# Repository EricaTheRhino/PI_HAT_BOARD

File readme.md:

# Erica HAT
A raspberry pi HAT containing the interfaces used on Erica.
This board has the hardware for all of Erica's functions, however only some will be populated on each pi

## Board modules

* **ID EEPROM** as per the hat specification.
* **Button and Status Indicator** to provide information on the state of the pi.
* **DC Input** allows powering of the pi through the HAT.
* **GPIO Breakout** an 8P8C connector containing broken out GPIO, used for the touch sensors.
* **Temperature Sensor** for measuring Erica's internal temperature.
* **Real Time Clock** maintains a time reference when Erica is powered off.
* **Webcam Led Controller** controls the brightness on the eye webcam LEDs also has USB passthough to the webcam.
* **Servo Connector** for connecting the eye servos (directly connected to gpio for use with servoblaster).
* **DMX Interface** for controlling DMX fixtures from the pi.
* **Debug USB-serial** connects to the pi's console for debugging.

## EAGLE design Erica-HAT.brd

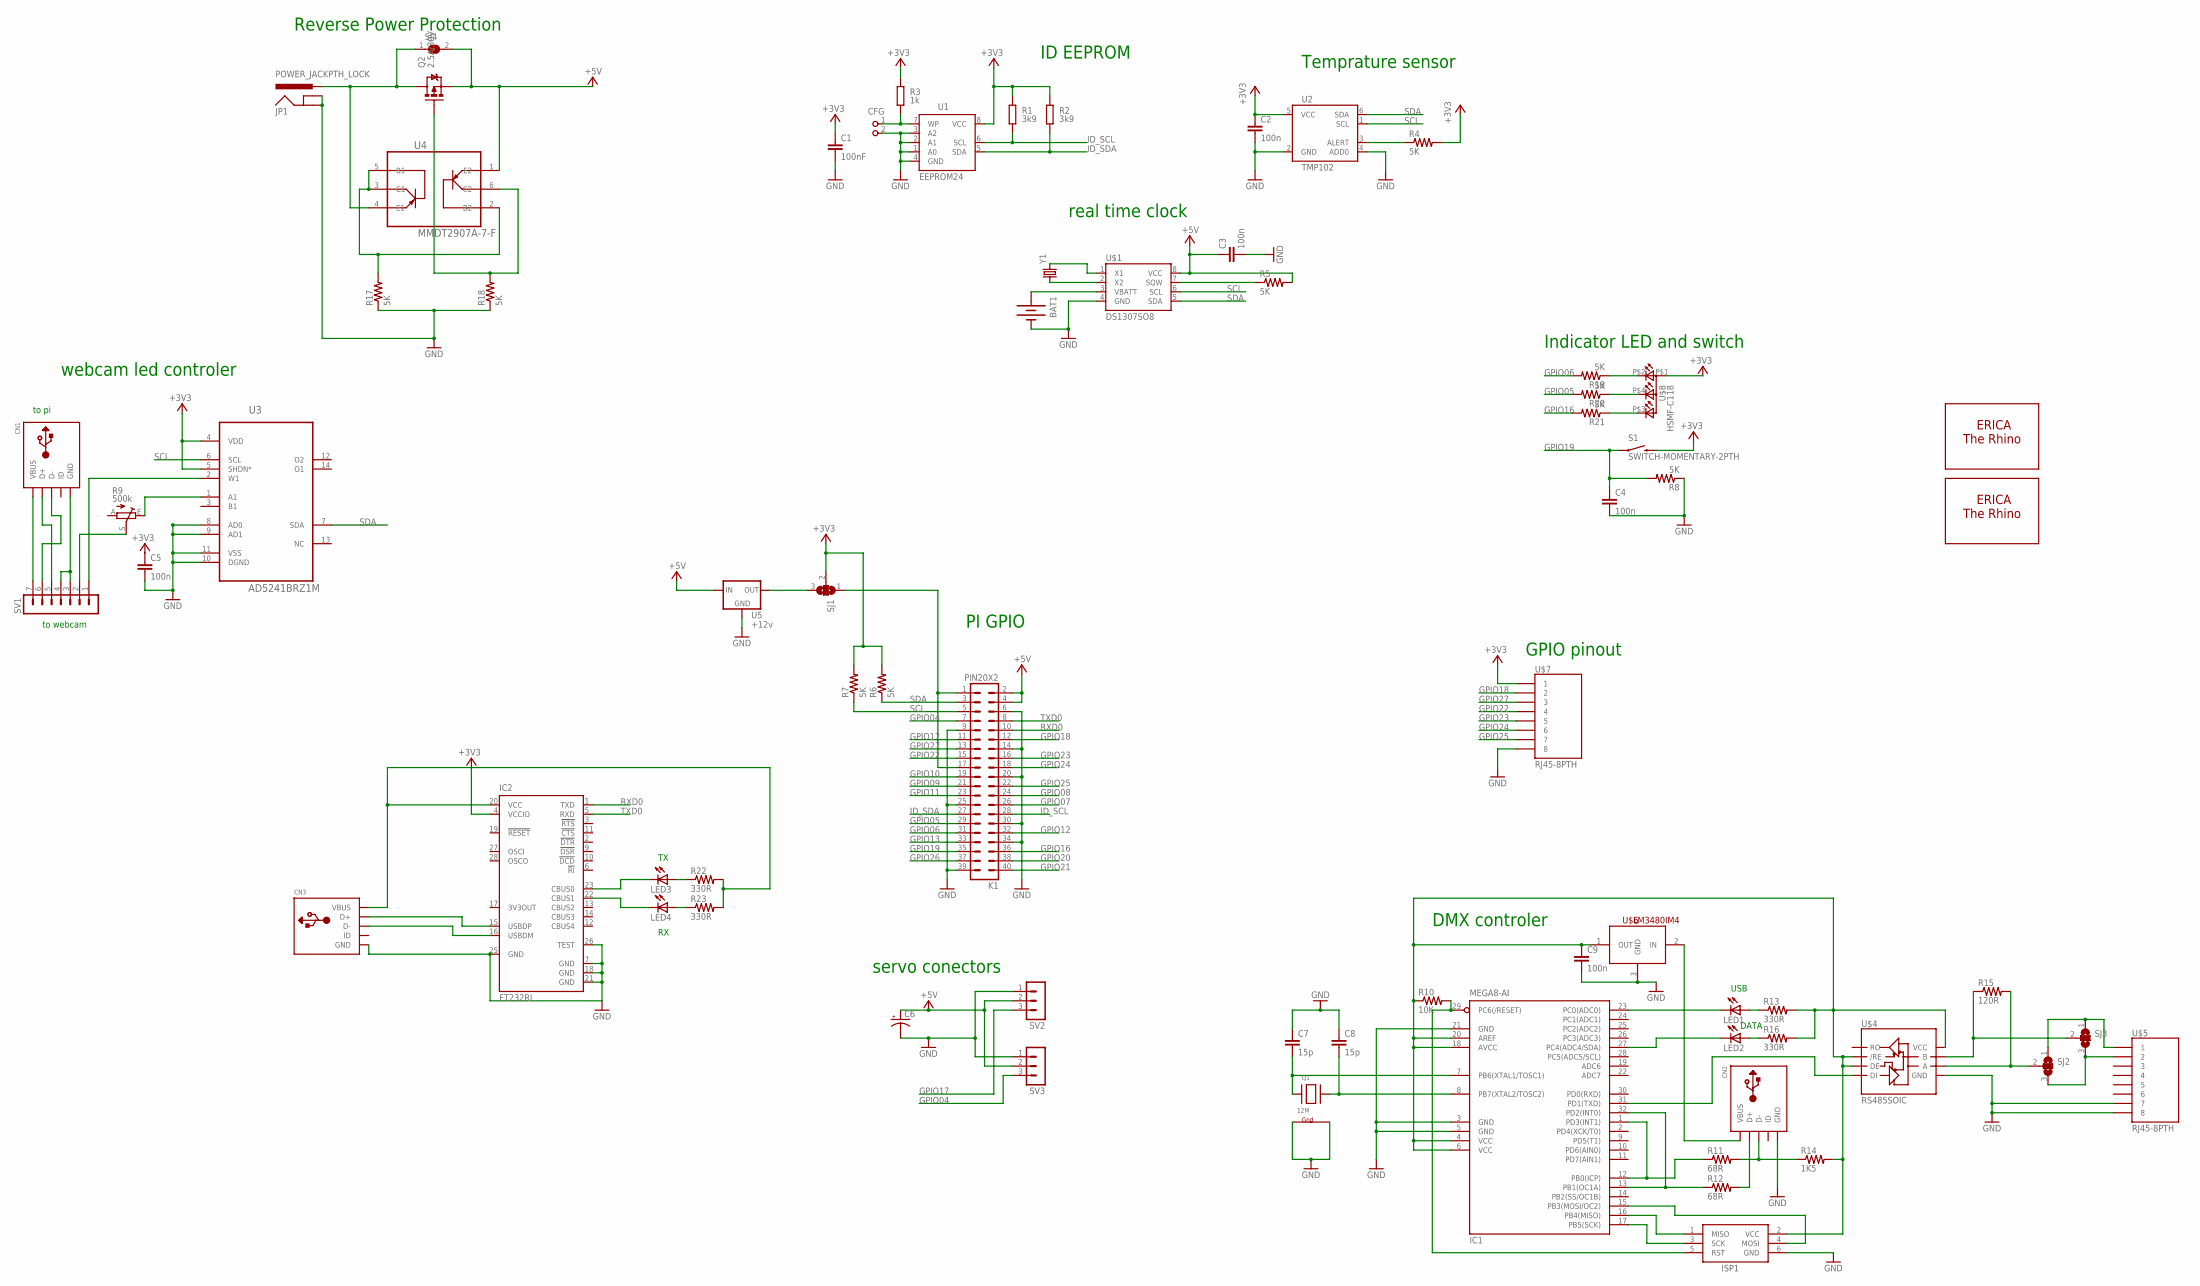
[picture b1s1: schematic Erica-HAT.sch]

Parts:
BAT1: BATTERY12MM; BATTCON_12MM
C1: 100nF; C0805K
C2, C3, C4, C5, C9: 100n; 0603-CAP
C6: CAP_POLPTH2; CPOL-RADIAL-10UF-25V
C7, C8: 15p; 0603-CAP
CFG: PIN2_100; PIN_W_2
CN1, CN2, CN3: USBMINIB; USB-MINIB
IC1: MEGA8-AI; TQFP32-08
IC2: FT232RL; SSOP28
ISP1: AVRISP-6; AVRISP
JP1: POWER_JACKPTH_LOCK; POWER_JACK_PTH_LOCK
K1: PIN20X2; PIN_20X2
LED1, LED2, LED3, LED4: LEDCHIP-LED0603; CHIP-LED0603
Q1: 12M; NX3225
Q2: 2.5A/30V; SOT23-3
R1, R2: 3k9; M0805; TOLERANCE 5%
R3: 1k; M0805; TOLERANCE 5%
R4, R5, R6, R7, R8, R17, R18, R19, R20, R21: 5K; 0603-RES
R9: 500k; B25U
R10: 10K; 0603-RES
R11, R12: 68R; 0603-RES
R13, R16, R22, R23: 330R; 0603-RES
R14: 1K5; 0603-RES
R15: 120R; 0603-RES
S1: SWITCH-MOMENTARY-2PTH; TACTILE-PTH
SJ1, SJ2, SJ3: SJ2W; SJ_2
SJ4: SJ
SV1: MA07-1
SV2, SV3: MA03-1
U1: EEPROM24; SOIC8
U2: TMP102; SOT563
U3: AD5241BRZ1M; SOIC127P600X175-14N
U4: MMDT2907A-7-F; SOT65P210X110-6N
U5: +12v; SOT223
U$1: DS1307SO8; SO08
U$2: ERICALOGO; ERICA_LOGO
U$3: ERICASILHOUETTE; ERICA_SILHOUETTE
U$4: RS485SOIC; SO08
U$5, U$7: RJ45-8PTH; RJ45-8
U$6: LM3480IM4; SOT23-3
U$8: HSMF-C118
Y1: CRYSTAL32-SMD; CRYSTAL-32KHZ-SMD

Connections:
+3V3: C1.1, C2.1, C5.1, IC2.4 (VCCIO), R1.2, R2.2, R3.2, R4.2, R6.2, R7.2, S1.3 (2), SJ1.2, U1.8 (VCC), U2.5 (VCC), U3.4 (VDD), U3.5 (SHDN*), U$7.1, U$8.P$1 (A2)
+5V: C3.1, C6.1 (+), K1.2, K1.4, Q2.2 (S), R5.2, SJ4.2, SV2.2, SV3.2, U4.1 (E2), U5.1 (IN), U$1.8 (VCC)
GND: BAT1.GND (-), C1.2, C2.2, C3.2, C4.2, C5.2, C6.2 (-), C7.1, C8.1, C9.2, CFG.2, CN2.GND, CN3.GND, IC1.3 (GND), IC1.5 (GND), IC1.21 (GND), IC2.7 (GND), IC2.18 (GND), IC2.21 (GND), IC2.25 (GND), IC2.26 (TEST), ISP1.6 (GND), JP1.GND, JP1.GNDBREAK, K1.6, K1.9, K1.14, K1.20, K1.25, K1.30, K1.34, K1.39, Q1.2 (G1), Q1.4 (G2), R8.1, R17.1, R18.1, SV2.1, SV3.1, U1.1 (A0), U1.2 (A1), U1.3 (A2), U1.4 (GND), U2.2 (GND), U2.4 (ADD0), U3.8 (AD0), U3.9 (AD1), U3.10 (DGND), U3.11 (VSS), U5.2 (GND), U$1.4 (GND), U$4.5 (GND), U$5.7, U$5.8, U$6.3 (GND), U$7.8
GPIO04: K1.7, SV3.3
GPIO05: K1.29, R20.2
GPIO06: K1.31, R19.2
GPIO07: K1.26
GPIO08: K1.24
GPIO09: K1.21
GPIO10: K1.19
GPIO11: K1.23
GPIO12: K1.32
GPIO13: K1.33
GPIO16: K1.36, R21.2
GPIO17: K1.11, SV2.3
GPIO18: K1.12, U$7.2
GPIO19: C4.1, K1.35, R8.2, S1.1
GPIO20: K1.38
GPIO21: K1.40
GPIO22: K1.15, U$7.4
GPIO23: K1.16, U$7.5
GPIO24: K1.18, U$7.6
GPIO25: K1.22, U$7.7
GPIO26: K1.37
GPIO27: K1.13, U$7.3
ID_SCL: K1.28, R1.1, U1.6 (SCL)
ID_SDA: K1.27, R2.1, U1.5 (SDA)
unnamed: R4.1, U2.3 (ALERT)
unnamed: BAT1.PWR@1 (+), U$1.3 (VBATT)
unnamed: CFG.1, R3.1, U1.7 (WP)
unnamed: R5.1, U$1.7 (SQW)
unnamed: R9.E, U3.1 (A1)
unnamed: R19.1, U$8.P$2 (CRED)
unnamed: U$1.1 (X1), Y1.X2 (2)
unnamed: U$1.2 (X2), Y1.X1 (1)
unnamed: R20.1, U$8.P$4 (CBLUE)
unnamed: R21.1, U$8.P$3 (CGREEN)
unnamed: SJ1.3, U5.3 (OUT)
unnamed: SJ2.1, SJ3.1, U$5.1
unnamed: CN1.GND, SV1.3, SV1.4
unnamed: CN1.D+, SV1.5
unnamed: CN1.D-, SV1.6
unnamed: CN1.VBUS, SV1.7
unnamed: SV1.1, U3.2 (W1)
unnamed: SJ2.3, SJ3.3, U$5.2
unnamed: R9.S, SV1.2
unnamed: C7.2, IC1.7 (PB6(XTAL1/TOSC1)), Q1.1 (X1)
unnamed: C8.2, IC1.8 (PB7(XTAL2/TOSC2)), Q1.3 (X2)
unnamed: IC1.29 (PC6(/RESET)), ISP1.5 (RST), R10.2
unnamed: IC1.13 (PB1(OC1A)), IC1.32 (PD2(INT0)), R12.1
unnamed: IC1.1 (PD3(INT1)), IC1.12 (PB0(ICP)), R11.1
unnamed: CN2.D-, R11.2, R14.1
unnamed: CN2.D+, R12.2
unnamed: IC1.23 (PC0(ADC0)), LED1.C
unnamed: LED1.A, R13.1
unnamed: IC1.31 (PD1(TXD)), U$4.4 (DI)
unnamed: C9.1, IC1.4 (VCC), IC1.6 (VCC), IC1.18 (AVCC), IC1.20 (AREF), ISP1.2 (VCC), R10.1, R13.2, R14.2, R16.2, U$4.2 (/RE), U$4.3 (DE), U$4.8 (VCC), U$6.1 (OUT)
unnamed: R15.1, SJ3.2, U$4.7 (B)
unnamed: R15.2, SJ2.2, U$4.6 (A)
unnamed: CN2.VBUS, U$6.2 (IN)
unnamed: IC1.16 (PB4(MISO)), ISP1.1 (MISO)
unnamed: IC1.17 (PB5(SCK)), ISP1.3 (SCK)
unnamed: IC1.15 (PB3(MOSI/OC2)), ISP1.4 (MOSI)
unnamed: IC1.27 (PC4(ADC4/SDA)), LED2.C
unnamed: JP1.PWR, Q2.3 (D), SJ4.1, U4.4 (E1)
unnamed: LED2.A, R16.1
unnamed: R17.2, U4.2 (B2), U4.3 (C1), U4.5 (B1)
unnamed: Q2.1 (G), R18.2, U4.6 (C2)
unnamed: LED3.A, R22.1
unnamed: CN3.D-, IC2.16 (USBDM)
unnamed: K1.1, K1.17, SJ1.1
unnamed: CN3.D+, IC2.15 (USBDP)
unnamed: LED4.A, R23.1
unnamed: IC2.23 (CBUS0), LED3.C
unnamed: IC2.22 (CBUS1), LED4.C
unnamed: CN3.VBUS, IC2.20 (VCC), R22.2, R23.2
RXD0: IC2.1 (TXD), K1.10
SCL: K1.5, R7.1, U2.1 (SCL), U3.6 (SCL), U$1.6 (SCL)
SDA: K1.3, R6.1, U2.6 (SDA), U3.7 (SDA), U$1.5 (SDA)
TXD0: IC2.5 (RXD), K1.8

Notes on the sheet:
ID EEPROM
PI GPIO
Temprature sensor
real time clock
Indicator LED and switch
to pi
to webcam
webcam led controler
servo conectors
DMX controler
GPIO pinout
Reverse Power Protection
USB
DATA

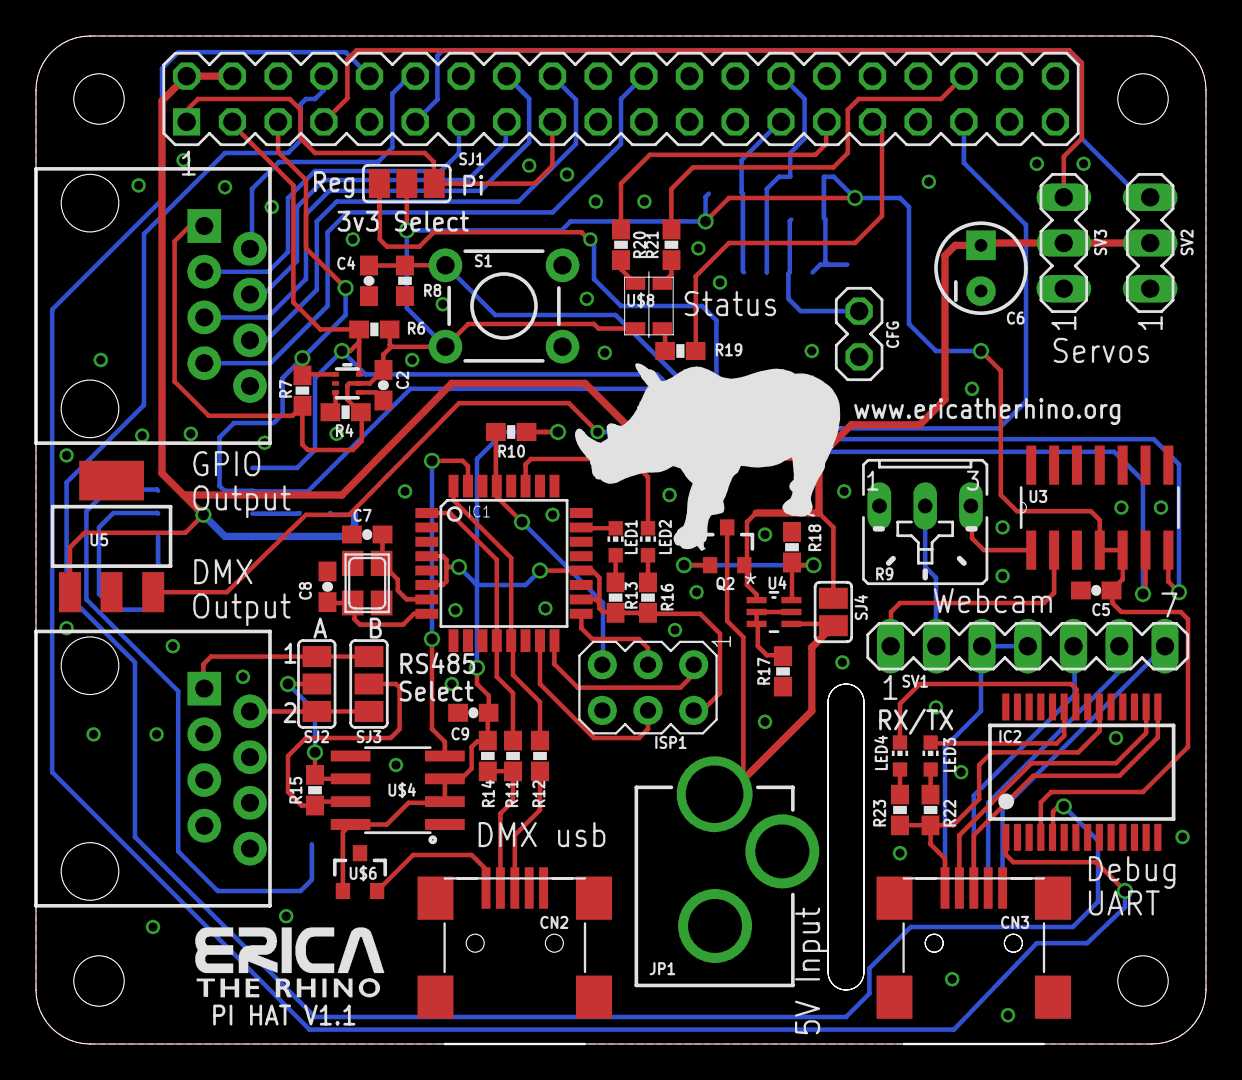
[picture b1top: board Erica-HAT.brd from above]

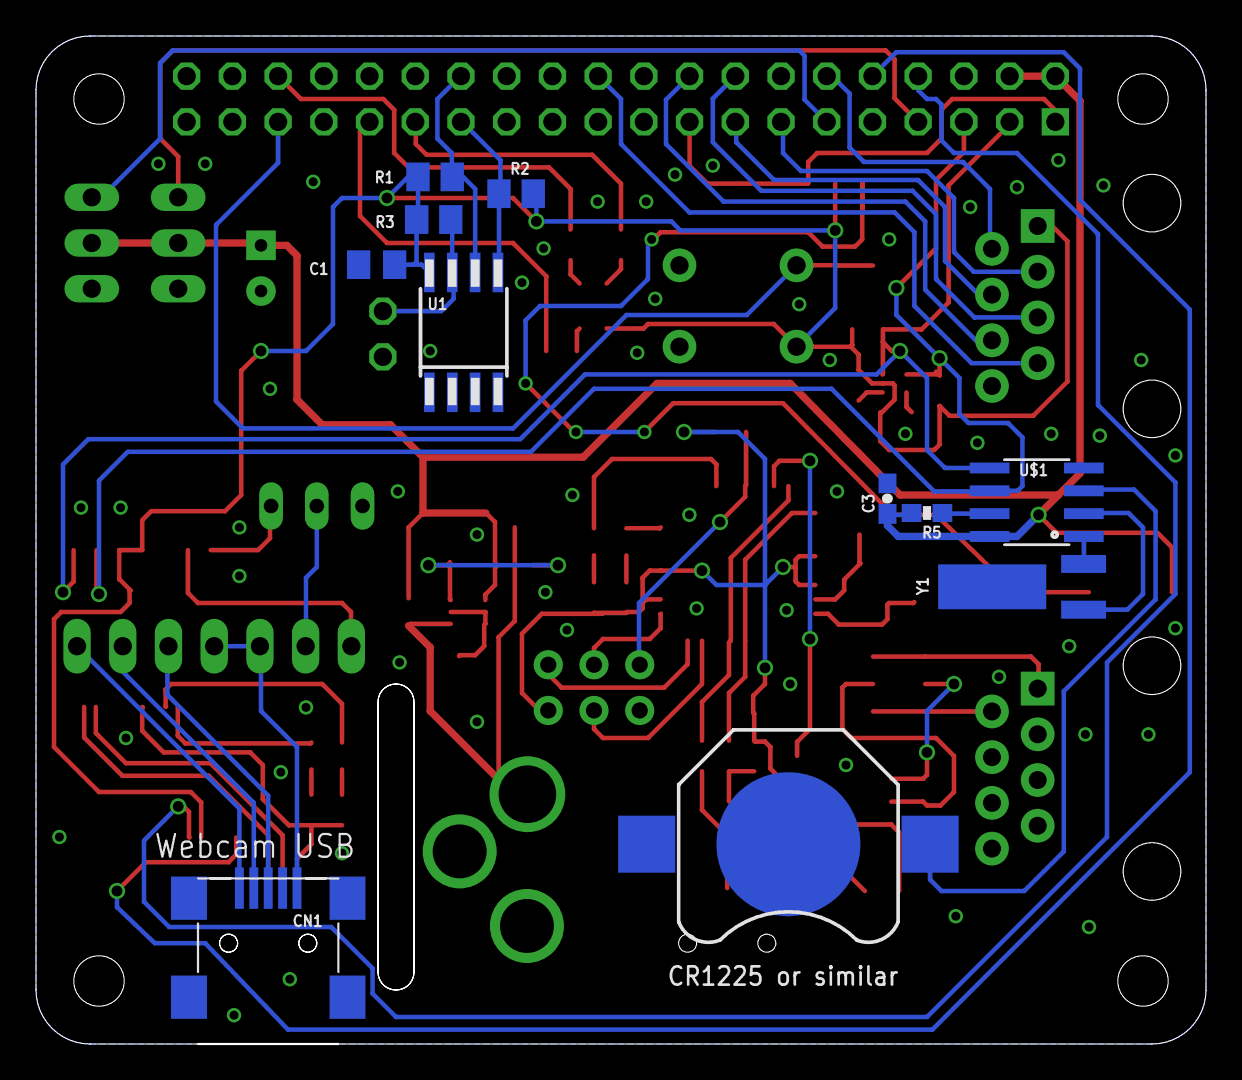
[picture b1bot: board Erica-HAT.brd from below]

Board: 2 copper layers, 65.0 x 56.0 mm, 70 parts (11 on the bottom side), 70 nets.

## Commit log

2015-02-16 Initial HAT PCB design
2015-02-16 Fixed remaining air wires. Added additional stitching. DRC clean.
2015-02-16 Added USB to serial for debug
2015-02-17 Added silkscreen labels
2015-02-17 Added more stitching vias. Hackvana DRC rules pass.
2015-02-18 changes for cam output
2015-02-18 Fixed URL and some other silkscreen issues
2015-02-25 Added readme and gitignore

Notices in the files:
parts and their libraries:
SparkFun-Sensors: Licensing: Creative Commons ShareAlike 4.0 International - https://creativecommons.org/licenses/by-sa/4.0
SparkFun: Licensing: CC v3.0 Share-Alike You are welcome to use this library for commercial purposes.
